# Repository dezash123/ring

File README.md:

## comparison

| ring                                                           | width   | thickness | sizes        | price                  |
| -------------------------------------------------------------- | ------- | --------- | ------------ | ---------------------- |
| mine                                                           | 7.0-7.6 | 2.4       | 5.5-infinite | ~$50                   |
| [circular](https://shop.circular.xyz/products/circular-ring-2) | 7.8     | 2.55      | 6-14         | $349                   |
| [oura](https://ouraring.com/store/rings/oura-ring-4)           | 7.9     | 2.88      | 4-15         | ($499 or $349) + $6/mo |
| [galaxy ring](https://www.samsung.com/us/rings/galaxy-ring/)   | 7.0     | 2.6       | 5-13         | $399                   |
| [ultrahuman](https://www.ultrahuman.com/ring/buy/us/)          | 8.1     | 2.45-2.8  | unclear      | $349                   |

6.9mm width can be made by inserting electronics mid-print
## pricing calculation
- jlcpcb: $186.59 for 2 assembled
	- board: $0.40
	- components: $26.38
	- SMT (per unit): $0.86
	- inspection: $3.14
	- everything else is fixed costs
- battery: $3.50
- casing: $0.08

total: $34.36
## features
- bq27427: battery monitor
- max30102: spo2 + heart rate
- lsm6dsox: accelerometer + gyro; provides step counter + gesture detection
- tmp117: skin temperature sensor
- im72d128v01: mic, higher-quality than most smartphones
- 17 mah battery

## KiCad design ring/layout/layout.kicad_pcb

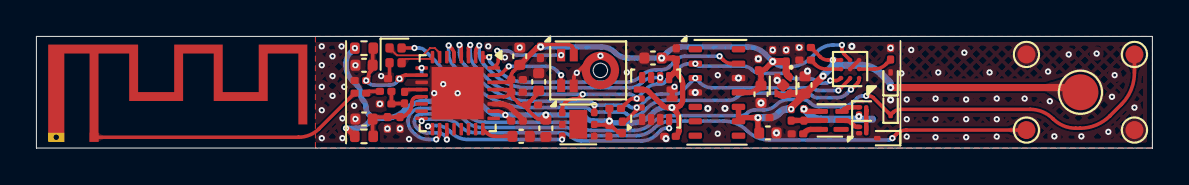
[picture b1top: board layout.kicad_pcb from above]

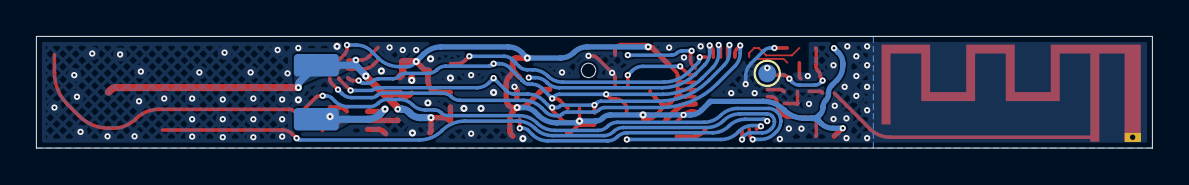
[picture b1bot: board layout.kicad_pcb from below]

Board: 2 copper layers, 62.0 x 6.2 mm, 62 parts (2 on the bottom side), 33 nets.

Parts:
C1, C30, C31: 1uF; C_0201_0603Metric
C2: 2.2uF; C_0201_0603Metric
C3, C6, C7, C11, C15, C18, C21, C23, C24, C25, C27, C28: 100nF; C_0201_0603Metric
C4, C8, C10, C16, C19, C26, C29: 1uF; C_0402_1005Metric
C5, C20: 10uF; C_0402_1005Metric
C9: 10nF; C_0201_0603Metric
C12: 1.6pF; C_0201_0603Metric
C13: 18pF; C_0201_0603Metric
C14, C17: 120pF; C_0201_0603Metric
C22: 4.7uF; C_0402_1005Metric
FB1, FB2: 0 0Hz; R_0402_1005Metric
L1: 2nH; L_0201_0603Metric
L2: 3.200000000000001nH; L_0201_0603Metric
R1, R2: 4.7k; R_0201_0603Metric
R3: 10k; R_0201_0603Metric
R4: 2.2k; R_0201_0603Metric
R5: 330; R_0201_0603Metric
TP1, TP3, TP4, TP5, TP6: TestPoint_Pad_D1.0mm
TP2: TestPoint_Pad_D2.0mm
U1: ?; BGA-9_1.6x1.6mm_Layout3x3_P0.5mm
U2: ?; Battery
U3, U4: ?; Texas_PicoStar_DFN-3_0.69x0.60mm
U5: ?; WSON-6_1.5x1.5mm_P0.5mm
U6: ?; QFN-32-1EP_4x4mm_P0.4mm_EP2.9x2.9mm
U7: ?; Texas_SWRA117D_2.4GHz_Right
U8: ?; Maxim_OLGA-14_3.3x5.6mm_P0.8mm
U9: ?; LGA-14_3x2.5mm_P0.5mm_LayoutBorder3x4y
U10: ?; Infineon_PG-LLGA-5-1
U11, U12, U13: ?; D_SOD-923
U14: ?; WSON-6-1EP_2x2mm_P0.65mm_EP1x1.6mm
U15: ?; Texas_X2SON-4_1x1mm_P0.65mm
Y1: 38.4MHz; Crystal_SMD_1210-4Pin_1.2x1.0mm

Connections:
GND: C1.2, C2.2, C4.2, C5.2, C6.2, C7.2, C8.2, C9.2, C10.2, C11.2, C12.2, C14.2, C15.2, C16.2, C17.2, C18.2, C19.2, C20.2, C21.2, C22.2, C23.2, C24.2, C25.2, C26.2, C27.2, C28.2, C29.2, C30.2, C31.2, R3.2, R4.2, TP5.1, TP6.1, U1.B2, U1.C1, U4.2, U6.11, U6.27, U6.33, U7.2, U8.4, U8.12, U9.1, U9.2, U9.3, U9.6, U9.7, U10.4, U10.5, U11.2, U12.2, U13.2, U14.2, U14.4, U15.2, U15.5, Y1.2, Y1.4
VBATT: C1.1, C20.1, C21.1, C29.1, R5.1, TP2.1, U1.C3, U2.1, U8.9, U8.10, U11.1, U15.3, U15.4
VDD: C5.1, C6.1, C7.1, C8.1, C9.1, C10.1, C11.1, C22.1, C23.1, C24.1, C25.1, C26.1, C27.1, C28.1, C30.1, C31.1, FB1.1, FB2.1, R1.1, R2.1, U1.C2, U6.26, U6.28, U6.29, U6.30, U8.11, U9.5, U9.8, U9.12, U10.2, U14.5, U15.1
bat_low: U1.A1, U6.5
batman.batman_vdd_out: C2.1, U1.B3
batman.bin: R3.1, U1.B1
battery.bat2: C3.1, R5.2, U5.5
battery.bat_cout: U4.1, U5.2
battery.bat_dout: U3.1, U5.3
battery.bat_qm: U3.3, U4.3
battery.bat_vm: R4.1, U5.6
battery.bat_vss: C3.2, U2.2, U3.2, U5.4
cpu.ant: L1.1, U6.12
cpu.ant.out1: C12.1, L1.2, L2.1
cpu.ant.out2: C13.1, L2.2
cpu.ant.out3: C13.2, U7.1
cpu.decouple: C4.1, U6.24
cpu.pavdd: C14.1, C15.1, C16.1, FB1.2, U6.13
cpu.rfvdd: C17.1, C18.1, C19.1, FB2.2, U6.10
cpu.xin: U6.7, Y1.1
cpu.xout: U6.8, Y1.3
hbt.NC: U8.1, U8.5, U8.6, U8.7, U8.8, U8.14
hbt_int: U6.1, U8.13
imu_int1: U6.16, U9.4
imu_int2: U6.2, U9.9
mic_clk: U6.31, U10.3
mic_data: U6.32, U10.1
rst: TP1.1, U6.9
scl: R2.2, U1.A3, U6.3, U8.2, U9.13, U14.1
sda: R1.2, U1.A2, U6.4, U8.3, U9.14, U14.6
swclk: TP4.1, U6.18, U13.1
swdio: TP3.1, U6.19, U12.1
tmp_int: U6.17, U14.3

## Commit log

2025-09-24 moved antenna and drc fully passes
2025-09-24 remove non-zener version
2025-09-24 pcb fully fully done
2025-09-24 refactor
2025-11-14 init
2025-11-14 readme
2025-11-14 formatting
2025-11-14 formatting2
